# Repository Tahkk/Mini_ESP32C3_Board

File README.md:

# Custom Mini ESP32-C3 Board
This project is a personal training to get familiar with PCB design
## Layers and schematic

<div align="center">
<br>
Schematic<br>
  
<br>
Top layer<br>

<br>
  Ground layer<br>
<br>
  Inside layer<br>
<br>
  Bottom layer<br>

</div>

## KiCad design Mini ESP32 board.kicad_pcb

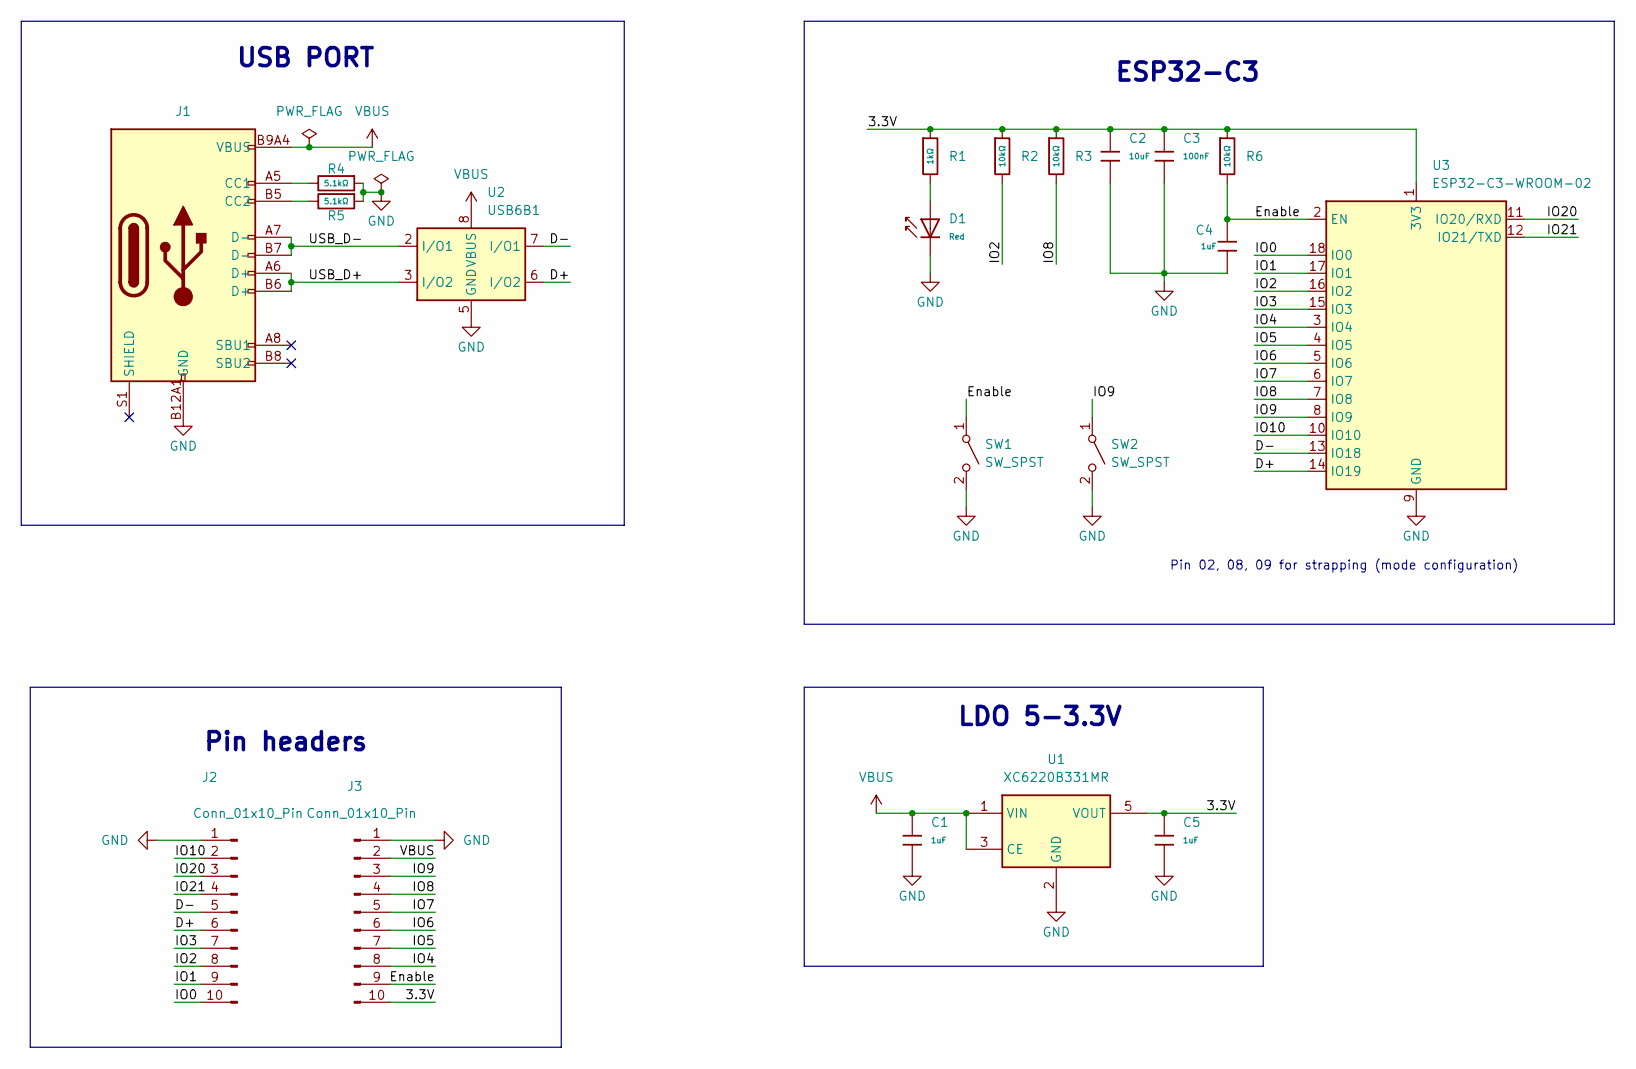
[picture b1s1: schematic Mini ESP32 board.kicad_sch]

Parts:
C1, C4, C5: 1uF; C_0603; Voltage Rated 50V; Tolerance ±10%; Part CL10A105KB8NNNC; LCSC C15849
C2: 10uF; C_0603; Voltage Rated 10V; Tolerance ±10%; Part CL10A106KP8NNNC; LCSC C19702
C3: 100nF; C_0603; Voltage Rated 50V; Tolerance ±10%; Part CC0603KRX7R9BB104; LCSC C14663
D1: Red; D_0603; Part KT-0603R; LCSC C2286
J1: Connector, USB-TYPE-C-16P; TYPE-C-SMD_HX-TYPE-C-16PIN; LCSC C2927039
J2, J3: Conn_01x10_Pin; PinSocket_1x10_P2.54mm_Vertical
R1: 1kΩ; R_0603; Overload Voltage (Max) 75V; Tolerance ±1%; Part 0603WAF1001T5E; LCSC C21190
R2, R3, R6: 10kΩ; R_0603; Overload Voltage (Max) 75V; Tolerance ±1%; Part 0603WAF1002T5E; LCSC C25804
R4, R5: 5.1kΩ; R_0603; Overload Voltage (Max) 75V; Tolerance ±1%; Part 0603WAF5101T5E; LCSC C23186
SW1, SW2: SW_SPST; SW_SPST_TS-1088-xR020
U1: XC6220B331MR; SOT-23-5
U2: USB6B1; SOIC-8_3.9x4.9mm_P1.27mm
U3: ESP32-C3-WROOM-02

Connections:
/3.3V: C2.1, C3.1, C5.1, J3.10, R1.1, R2.1, R3.1, R6.1, U1.5 (VOUT), U3.1 (3V3)
/D+: J2.6, U2.6 (I/O2), U3.14 (IO19)
/D-: J2.5, U2.7 (I/O1), U3.13 (IO18)
/Enable: C4.1, J3.9, R6.2, SW1.1 (A), U3.2 (EN)
/IO0: J2.10, U3.18 (IO0)
/IO1: J2.9, U3.17 (IO1)
/IO2: J2.8, R2.2, U3.16 (IO2)
/IO3: J2.7, U3.15 (IO3)
/IO4: J3.8, U3.3 (IO4)
/IO5: J3.7, U3.4 (IO5)
/IO6: J3.6, U3.5 (IO6)
/IO7: J3.5, U3.6 (IO7)
/IO8: J3.4, R3.2, U3.7 (IO8)
/IO9: J3.3, SW2.1 (A), U3.8 (IO9)
/IO10: J2.2, U3.10 (IO10)
/IO20: J2.3, U3.11 (IO20/RXD)
/IO21: J2.4, U3.12 (IO21/TXD)
/USB_D+: J1.A6 (D+), J1.B6 (D+), U2.3 (I/O2)
/USB_D-: J1.A7 (D-), J1.B7 (D-), U2.2 (I/O1)
GND: C1.2, C2.2, C3.2, C4.2, C5.2, D1.1, J1.A12B1 (GND), J1.B12A1 (GND), J2.1, J3.1, R4.1, R5.1, SW1.2 (B), SW2.2 (B), U1.2 (GND), U2.4 (GND), U2.5 (GND), U3.9 (GND), U3.19 (GND)
unnamed: D1.2, R1.2
unnamed: J1.A5 (CC1), R4.2
unnamed: J1.B5 (CC2), R5.2
VBUS: C1.1, J1.A9B4 (VBUS), J1.B9A4 (VBUS), J3.2, U1.1 (VIN), U1.3 (CE), U2.1 (VBUS), U2.8 (VBUS)

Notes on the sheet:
Pin 02, 08, 09 for strapping (mode configuration)
USB PORT
Pin headers
ESP32-C3
LDO 5-3.3V

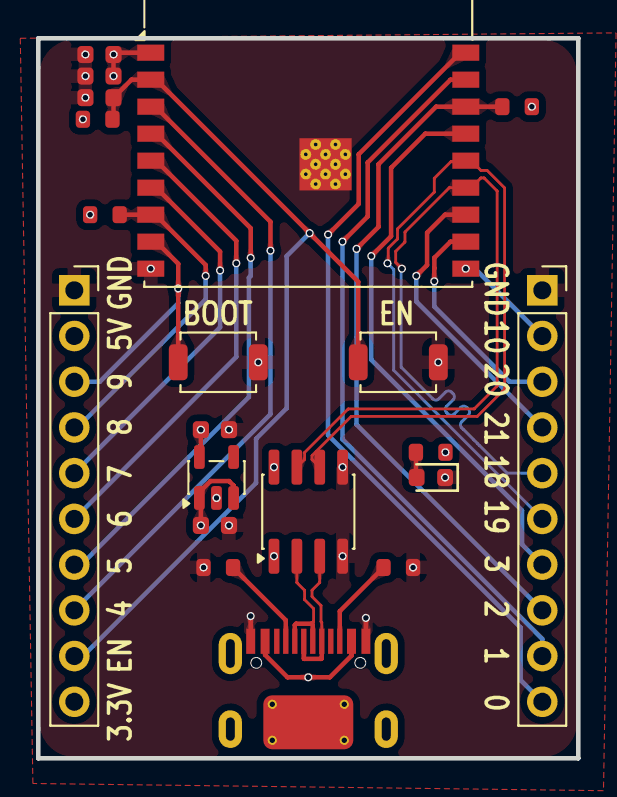
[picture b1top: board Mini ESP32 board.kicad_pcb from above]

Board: 4 copper layers, 30.0 x 40.0 mm, 20 parts (0 on the bottom side), 24 nets.

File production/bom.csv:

Designator,Footprint,Quantity,Value,LCSC Part #
"C1, C4, C5",C_0603,3,1uF,C15849
C2,C_0603,1,10uF,C19702
C3,C_0603,1,100nF,C14663
D1,D_0603,1,Red,C2286
J1,TYPE-C-SMD_HX-TYPE-C-16PIN,1,"Connector, USB-TYPE-C-16P",C2927039
"J2, J3",PinSocket_1x10_P2.54mm_Vertical,2,Conn_01x10_Pin,
R1,R_0603,1,1kΩ,C21190
"R2, R3, R6",R_0603,3,10kΩ,C25804
"R4, R5",R_0603,2,5.1kΩ,C23186
"SW1, SW2",SW_SPST_TS-1088-xR020,2,SW_SPST,
U1,SOT-23-5,1,XC6220B331MR,
U2,SOIC-8_3.9x4.9mm_P1.27mm,1,USB6B1,
U3,ESP32-C3-WROOM-02,1,ESP32-C3-WROOM-02,
